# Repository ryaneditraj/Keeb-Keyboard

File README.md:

# Keeb Keyboard

A 64-key open-source mechanical keyboard: an ANSI 60% layout, a 4-key arrow cluster, a Raspberry Pi Pico, and a glue-in case. The schematic, PCB, Gerbers, and STEP file are the whole project.

Built for [Hack Club KEEB](https://keeb.hackclub.com/), a you-ship-we-ship mechanical keyboard project. This was Ryan Editraj's first PCB: a 60% he extended with arrow keys, routed in KiCad, with the Pico soldered on the front and the case modeled in Onshape.

## Demo

This repository has no firmware and no app, so there is no device screen to capture. KiCad 10 is not installed in a stock Ubuntu image, and these pictures were **plotted from the design files** by [`scripts/render_previews.py`](scripts/render_previews.py). They are not photographs and not exports from KiCad's 3D viewer.

In KiCad's default Y-up view the number row sits toward the bottom of the canvas. The plots above put that row at the top, which is how the board sits on a desk. USB leaves the far edge.

## Features

* **64 MX-style keys.** 60 keys in an ANSI 60% unit layout, plus four 1u arrow keys stepped in on the right.
* **Cherry MX PCB-mount footprints** from KiCad's keyboard library, in 1u, 1.25u, 1.5u, 1.75u, 2u, 2.25u, 2.75u, and 6.25u.
* **One diode per switch.** 64 DO-35 through-hole diodes (the KEEB parts list uses 1N4148). Cathodes face the rows, which is COL2ROW.
* **Five PCB-mount stabilizers** from marbastlib: 2u under the 2u, 2.25u, and 2.75u keys, and 6.25u under the spacebar.
* **Raspberry Pi Pico** on the common module footprint (Pico, Pico W, or Pico 2 pinout). It sits on the front of the board, in the top-right bay, with USB-C hanging off the top edge.
* **5 × 17 keyboard matrix** (ROW0–ROW4, COL0–COL16) on GP0–GP21. 64 of the 85 positions are filled.
* **Two-layer, 1.6 mm board.** 575 traces, almost all through-hole, so the design only needs two vias.
* **Fabrication outputs included.** Gerbers and Excellon drills in `PCB FILES/Output.zip`, exported from KiCad 10.0.4.
* **Onshape case.** A single open tray, about 334 × 105 × 11 mm, meant to be glued with PE foam in the bottom. No plate and no mounting holes.

## Layout

Unit sizes below are read from the footprints. The schematic does not store key legends, so this README does not invent a QWERTY print. The sizes themselves match an ANSI 60%.

| Row | Keys | Widths, left to right |
| --- | --- | --- |
| 0 | 14 | 13 × 1u, 2u |
| 1 | 14 | 1.5u, 12 × 1u, 1.5u |
| 2 | 13 | 1.75u, 11 × 1u, 2.25u |
| 3 | 12 | 2.25u, 10 × 1u, 2.75u |
| 4 | 7 | 1.25u × 3, 6.25u, 1.25u × 3 |
| Arrows | 4 | 1u up, then 1u left / down / right, set slightly below the right side |

The Pico occupies the empty bay to the right of rows 0–2, above the arrow cluster.

## Tech stack

| Piece | Choice |
| --- | --- |
| Schematic and PCB | [KiCad](https://www.kicad.org/) 10.0.4 |
| Switch footprints | `Switch_Keyboard_Cherry_MX:SW_Cherry_MX_PCB_*` |
| Stabilizers | [marbastlib](https://github.com/ebastler/marbastlib) `STAB_MX_2u` and `STAB_MX_6.25u` |
| Diodes | `Device:D_Small` on `Diode_THT:D_DO-35_SOD27_P7.62mm_Horizontal` |
| Microcontroller | Raspberry Pi Pico, `Module:RaspberryPi_Pico_Common_Unspecified` |
| Case | Onshape, exported as STEP AP242 |
| Firmware | Not in this repo yet. [KEEB's firmware guide](https://keeb.hackclub.com/docs/firmware/) points at RMK. Any scanner that can drive a COL2ROW matrix can use the pinout below. |
| CI | GitHub Actions runs `scripts/check_design.py` (Python stdlib only) |

## Quick start

1. Install [KiCad 10](https://www.kicad.org/) or newer. Older KiCad releases will not open the files.
2. Install marbastlib. In KiCad's Plugin and Content Manager, add `https://raw.githubusercontent.com/ebastler/ebastler-KiCad-repository/main/repository.json`, then install **marbastlib**. The KEEB doc [Designing the PCB](https://keeb.hackclub.com/docs/pcb-design/) has the click path.
3. Open the two design files directly. There is no `.kicad_pro` in the repo.

```text
PCB FILES/keyboard.kicad_sch
PCB FILES/keyboard.kicad_pcb
```

4. Check that the files still match the reviewed design:

```bash
python3 scripts/check_design.py
```

5. To redraw the pictures in `docs/images/`:

```bash
pip install pillow
python3 scripts/render_previews.py
```

No environment variables are required. See [.env.example](.env.example).

## Usage

### Read the board

Switches are `SW1`–`SW64`, diodes `D1`–`D64`, stabilizers `ST14`, `ST41`, `ST42`, `ST53`, and `ST58`, and the Pico is `A1`. Rows and columns are global labels (`ROW0`–`ROW4`, `COL0`–`COL16`).

### Order the PCB

`PCB FILES/Output.zip` is a KiCad 10.0.4 fabrication set:

| File | Layer |
| --- | --- |
| `keyboard-F_Cu.gbr` / `keyboard-B_Cu.gbr` | Front and back copper |
| `keyboard-F_Mask.gbr` / `keyboard-B_Mask.gbr` | Solder mask |
| `keyboard-F_Silkscreen.gbr` / `keyboard-B_Silkscreen.gbr` | Silkscreen |
| `keyboard-F_Paste.gbr` / `keyboard-B_Paste.gbr` | Paste (empty of parts; this is a through-hole board) |
| `keyboard-Edge_Cuts.gbr` | Board outline, 328.5 × 100.5 mm |
| `keyboard-PTH.drl` / `keyboard-NPTH.drl` | Plated and non-plated drills |

Ask the fab for a 2-layer, 1.6 mm board. Traces are 0.2 mm and the two vias are a 0.3 mm drill in a 0.6 mm pad, so check the fab's minimums before you order. Details are in [SECURITY.md](SECURITY.md#design-notes-that-are-not-code-vulnerabilities).

### Bill of materials

| Qty | Refs | Part | Footprint |
| --- | --- | --- | --- |
| 64 | SW1–SW64 | MX-compatible PCB-mount switch | Cherry MX PCB, see the layout table for sizes |
| 64 | D1–D64 | Small-signal diode, DO-35 (KEEB uses 1N4148) | Horizontal, 7.62 mm pitch |
| 4 | ST14, ST41, ST42, ST53 | PCB-mount MX stabilizer, 2u | marbastlib `STAB_MX_2u` |
| 1 | ST58 | PCB-mount MX stabilizer, 6.25u | marbastlib `STAB_MX_6.25u` |
| 1 | A1 | Raspberry Pi Pico (Pico W and Pico 2 fit the same footprint) | Common Pico module |
| 1 | — | Keycaps to match the unit sizes | — |
| 1 | — | Case tray, or print/cut your own from the STEP | Onshape part |

The schematic symbol for the diode is `D_Small`, not a locked manufacturer part number. Match the DO-35 footprint.

### Matrix pinout

Diode footprint pin 1 is the cathode and lands on the row. The switch connects the column to the diode anode. Drive columns, read rows (COL2ROW).

GPIO names are the official Raspberry Pi Pico pinout for these pad numbers. The unused pads in the KiCad footprint use that same numbering (`GPIO22-Pad29`, `GPIO26_ADC0-Pad31`, and so on).

| Net | Pico pin | GPIO |
| --- | --- | --- |
| ROW0 | 1 | GP0 |
| ROW1 | 2 | GP1 |
| ROW2 | 4 | GP2 |
| ROW3 | 5 | GP3 |
| ROW4 | 6 | GP4 |
| COL0 | 7 | GP5 |
| COL1 | 9 | GP6 |
| COL2 | 10 | GP7 |
| COL3 | 11 | GP8 |
| COL4 | 12 | GP9 |
| COL5 | 14 | GP10 |
| COL6 | 15 | GP11 |
| COL7 | 16 | GP12 |
| COL8 | 17 | GP13 |
| COL9 | 19 | GP14 |
| COL10 | 20 | GP15 |
| COL11 | 21 | GP16 |
| COL12 | 22 | GP17 |
| COL13 | 24 | GP18 |
| COL14 | 25 | GP19 |
| COL15 | 26 | GP20 |
| COL16 | 27 | GP21 |

Pico pins 3, 8, 13, 18, 23, 28, and 38 are ground and are tied together on the module footprint. GP22, the ADC pins, RUN, 3V3, and VBUS stay on the module. That is what you want when the Pico's own regulator and USB connector do the power.

### Open the case

Import `Case Files/keeb - Part 579.step` into Onshape, Fusion 360, or FreeCAD. The solid is one open tray: 334.4 × 104.9 × 11.0 mm outside, with a cavity 331.4 × 102.5 mm, a 4 mm floor, and walls that rise 7 mm. Wall thickness is uneven, about 1.3–1.7 mm along the length and 1.1–1.3 mm along the depth. The PCB (328.5 × 100.5 mm) drops into that cavity. The original plan is glue plus PE foam, which matches a board with no mounting holes.

## Project structure

```text
.
├── PCB FILES/
│   ├── keyboard.kicad_sch    # schematic, KiCad 10
│   ├── keyboard.kicad_pcb     # 2-layer board
│   └── Output.zip             # Gerbers and drills
├── Case Files/
│   └── keeb - Part 579.step   # Onshape tray
├── docs/images/               # plots generated from those files
├── scripts/
│   ├── check_design.py        # CI check, stdlib only
│   └── render_previews.py     # rebuild the plots (needs Pillow)
├── .github/                   # CI, issue forms, pull request template
├── LICENSE                    # MIT
├── CONTRIBUTING.md
├── CODE_OF_CONDUCT.md
├── SECURITY.md
└── .env.example               # no secrets; nothing reads this
```

Folder names keep the spaces they were published with.

## Roadmap

* Firmware and a keymap (RMK, KMK, or QMK) that uses the pinout above.
* A photo of the soldered board, once it exists. The plots in this README are not a stand-in for that.
* Mounting holes, if the case moves off glue and foam.
* A plate, if the tray gets a top half.
* A design-rule pass before the next fab order: 0.2 mm traces, 0.3 / 0.6 mm vias, and the tight outline.
* Hotswap sockets. The footprints today are soldered PCB-mount MX.

## FAQ

### What is Keeb Keyboard?

Keeb Keyboard is an open-source 64-key mechanical keyboard design by Ryan Editraj. It is a KiCad PCB for a Raspberry Pi Pico, plus an Onshape case, published for Hack Club KEEB.

### Is this a 60% keyboard?

The alpha block is a 60-key ANSI 60% (right shift is 2.75u, so there is no extra 1u key beside it). Four arrow keys bring the switch count to 64. It is not a 65% or a 75%.

### Which microcontroller does it use?

A Raspberry Pi Pico, soldered on the front of the board in the top-right bay. The footprint also fits a Pico W or a Pico 2. The matrix uses GP0 through GP21. Wireless pins are unused.

### What switches and diodes does the PCB use?

MX-compatible PCB-mount switches in Cherry MX footprints, one DO-35 small-signal diode per switch, and PCB-mount MX stabilizers on the wide keys. The KEEB build guide uses 1N4148 diodes for this footprint.

### How do I open the design files?

Install KiCad 10 or newer and marbastlib, then open `PCB FILES/keyboard.kicad_sch` and `PCB FILES/keyboard.kicad_pcb`. There is no KiCad project file to double-click.

### How do I flash the firmware?

You can't yet. Firmware is not in the repository. The [matrix pinout](#matrix-pinout) is the map a firmware needs. Hack Club's guide recommends [RMK](https://keeb.hackclub.com/docs/firmware/).

### Can I manufacture this board?

Yes. The Gerbers and drills are in `PCB FILES/Output.zip`. It is a 2-layer, 1.6 mm, through-hole keyboard PCB, 328.5 × 100.5 mm. Read the fabrication notes before ordering: thin traces, small vias, no mounting holes.

### What is the case file?

`Case Files/keeb - Part 579.step` is a single Onshape tray, roughly 334 × 105 × 11 mm, sized to hold the PCB with glue and PE foam. It is not a full sandwich case and it has no switch plate.

### Are there API keys or secrets in the repository?

No. The design files, Gerbers, STEP file, and git history were scanned. Nothing needs to be rotated. Manufacturing files are public on purpose.

### Who is allowed to build or modify this?

Anyone. The design is MIT licensed. Keep the copyright notice if you redistribute it.

### Who made this?

Ryan Editraj, while learning schematic capture, PCB layout, and CAD for Hack Club KEEB. The Pico is on the front of the board because mounting it on the back was not obvious yet, and the journaling habit started late in the build.

## Contributing

See [CONTRIBUTING.md](CONTRIBUTING.md). Small, specific pull requests are the useful ones: a footprint fix, a regenerated Gerber zip, firmware that matches this matrix, or a clearer note. Please follow the [Code of Conduct](CODE_OF_CONDUCT.md).

## License

[MIT](LICENSE) © 2026 Ryan Editraj.

## Author

**Ryan Editraj** — AI builder and tech creator.

* GitHub: [github.com/ryaneditraj](https://github.com/ryaneditraj)
* Instagram: [instagram.com/ryaneditraj](https://instagram.com/ryaneditraj)

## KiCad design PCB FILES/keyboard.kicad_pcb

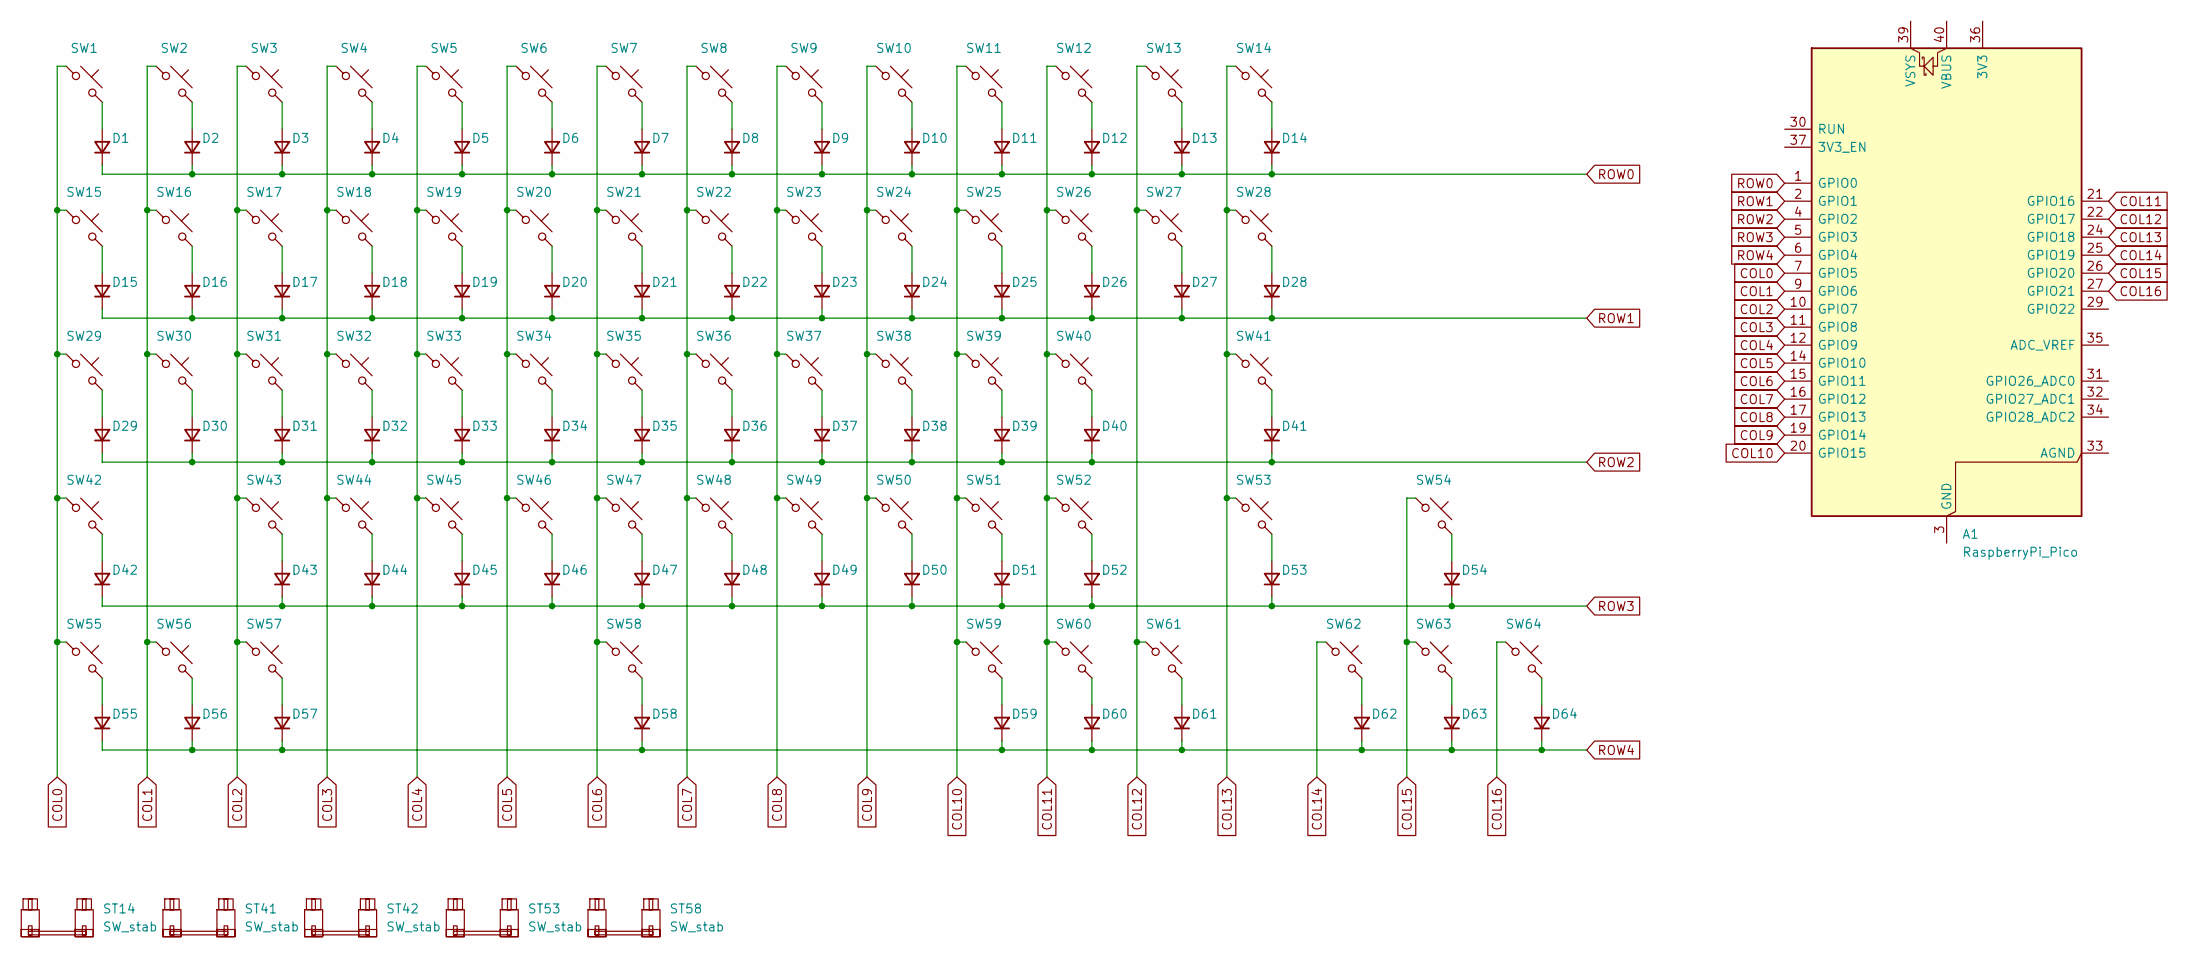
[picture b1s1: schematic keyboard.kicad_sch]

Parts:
A1: RaspberryPi_Pico; RaspberryPi_Pico_Common_Unspecified
D1, D2, D3, D4, D5, D6, D7, D8, D9, D10, D11, D12, D13, D14, D15, D16, D17, D18, D19, D20, D21, D22, D23, D24, D25, D26, D27, D28, D29, D30, D31, D32, D33, D34, D35, D36, D37, D38, D39, D40, D41, D42, D43, D44, D45, D46, D47, D48, D49, D50, D51, D52, D53, D54, D55, D56, D57, D58, D59, D60, D61, D62, D63, D64: D; D_DO-35_SOD27_P7.62mm_Horizontal
ST14, ST41, ST42, ST53: SW_stab; STAB_MX_2u
ST58: SW_stab; STAB_MX_6.25u
SW1, SW2, SW3, SW4, SW5, SW6, SW7, SW8, SW9, SW10, SW11, SW12, SW13, SW16, SW17, SW18, SW19, SW20, SW21, SW22, SW23, SW24, SW25, SW26, SW27, SW30, SW31, SW32, SW33, SW34, SW35, SW36, SW37, SW38, SW39, SW40, SW43, SW44, SW45, SW46, SW47, SW48, SW49, SW50, SW51, SW52, SW54, SW62, SW63, SW64: SW_Push; SW_Cherry_MX_PCB_1.00u
SW14: SW_Push; SW_Cherry_MX_PCB_2.00u
SW15, SW28: SW_Push; SW_Cherry_MX_PCB_1.50u
SW29: SW_Push; SW_Cherry_MX_PCB_1.75u
SW41, SW42: SW_Push; SW_Cherry_MX_PCB_2.25u
SW53: SW_Push; SW_Cherry_MX_PCB_2.75u
SW55, SW56, SW57, SW59, SW60, SW61: SW_Push; SW_Cherry_MX_PCB_1.25u
SW58: SW_Push; SW_Cherry_MX_PCB_6.25u

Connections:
COL0: A1.7 (GPIO5), SW1.1, SW15.1, SW29.1, SW42.1, SW55.1
COL1: A1.9 (GPIO6), SW2.1, SW16.1, SW30.1, SW56.1
COL2: A1.10 (GPIO7), SW3.1, SW17.1, SW31.1, SW43.1, SW57.1
COL3: A1.11 (GPIO8), SW4.1, SW18.1, SW32.1, SW44.1
COL4: A1.12 (GPIO9), SW5.1, SW19.1, SW33.1, SW45.1
COL5: A1.14 (GPIO10), SW6.1, SW20.1, SW34.1, SW46.1
COL6: A1.15 (GPIO11), SW7.1, SW21.1, SW35.1, SW47.1, SW58.1
COL7: A1.16 (GPIO12), SW8.1, SW22.1, SW36.1, SW48.1
COL8: A1.17 (GPIO13), SW9.1, SW23.1, SW37.1, SW49.1
COL9: A1.19 (GPIO14), SW10.1, SW24.1, SW38.1, SW50.1
COL10: A1.20 (GPIO15), SW11.1, SW25.1, SW39.1, SW51.1, SW59.1
COL11: A1.21 (GPIO16), SW12.1, SW26.1, SW40.1, SW52.1, SW60.1
COL12: A1.22 (GPIO17), SW13.1, SW27.1, SW61.1
COL13: A1.24 (GPIO18), SW14.1, SW28.1, SW41.1, SW53.1
COL14: A1.25 (GPIO19), SW62.1
COL15: A1.26 (GPIO20), SW54.1, SW63.1
COL16: A1.27 (GPIO21), SW64.1
unnamed: A1.3 (GND), A1.8 (GND), A1.13 (GND), A1.18 (GND), A1.23 (GND), A1.28 (GND), A1.38 (GND)
unnamed: D1.2 (A), SW1.2
unnamed: D2.2 (A), SW2.2
unnamed: D3.2 (A), SW3.2
unnamed: D4.2 (A), SW4.2
unnamed: D5.2 (A), SW5.2
unnamed: D6.2 (A), SW6.2
unnamed: D7.2 (A), SW7.2
unnamed: D8.2 (A), SW8.2
unnamed: D9.2 (A), SW9.2
unnamed: D10.2 (A), SW10.2
unnamed: D11.2 (A), SW11.2
unnamed: D12.2 (A), SW12.2
unnamed: D13.2 (A), SW13.2
unnamed: D14.2 (A), SW14.2
unnamed: D15.2 (A), SW15.2
unnamed: D16.2 (A), SW16.2
unnamed: D17.2 (A), SW17.2
unnamed: D18.2 (A), SW18.2
unnamed: D19.2 (A), SW19.2
unnamed: D20.2 (A), SW20.2
unnamed: D21.2 (A), SW21.2
unnamed: D22.2 (A), SW22.2
unnamed: D23.2 (A), SW23.2
unnamed: D24.2 (A), SW24.2
unnamed: D25.2 (A), SW25.2
unnamed: D26.2 (A), SW26.2
unnamed: D27.2 (A), SW27.2
unnamed: D28.2 (A), SW28.2
unnamed: D29.2 (A), SW29.2
unnamed: D30.2 (A), SW30.2
unnamed: D31.2 (A), SW31.2
unnamed: D32.2 (A), SW32.2
unnamed: D33.2 (A), SW33.2
unnamed: D34.2 (A), SW34.2
unnamed: D35.2 (A), SW35.2
unnamed: D36.2 (A), SW36.2
unnamed: D37.2 (A), SW37.2
unnamed: D38.2 (A), SW38.2
unnamed: D39.2 (A), SW39.2
unnamed: D40.2 (A), SW40.2
unnamed: D41.2 (A), SW41.2
unnamed: D42.2 (A), SW42.2
unnamed: D43.2 (A), SW43.2
unnamed: D44.2 (A), SW44.2
unnamed: D45.2 (A), SW45.2
unnamed: D46.2 (A), SW46.2
unnamed: D47.2 (A), SW47.2
unnamed: D48.2 (A), SW48.2
unnamed: D49.2 (A), SW49.2
unnamed: D50.2 (A), SW50.2
unnamed: D51.2 (A), SW51.2
unnamed: D52.2 (A), SW52.2
unnamed: D53.2 (A), SW53.2
unnamed: D54.2 (A), SW54.2
unnamed: D55.2 (A), SW55.2
unnamed: D56.2 (A), SW56.2
unnamed: D57.2 (A), SW57.2
unnamed: D58.2 (A), SW58.2
unnamed: D59.2 (A), SW59.2
unnamed: D60.2 (A), SW60.2
unnamed: D61.2 (A), SW61.2
unnamed: D62.2 (A), SW62.2
unnamed: D63.2 (A), SW63.2
unnamed: D64.2 (A), SW64.2
ROW0: A1.1 (GPIO0), D1.1 (K), D2.1 (K), D3.1 (K), D4.1 (K), D5.1 (K), D6.1 (K), D7.1 (K), D8.1 (K), D9.1 (K), D10.1 (K), D11.1 (K), D12.1 (K), D13.1 (K), D14.1 (K)
ROW1: A1.2 (GPIO1), D15.1 (K), D16.1 (K), D17.1 (K), D18.1 (K), D19.1 (K), D20.1 (K), D21.1 (K), D22.1 (K), D23.1 (K), D24.1 (K), D25.1 (K), D26.1 (K), D27.1 (K), D28.1 (K)
ROW2: A1.4 (GPIO2), D29.1 (K), D30.1 (K), D31.1 (K), D32.1 (K), D33.1 (K), D34.1 (K), D35.1 (K), D36.1 (K), D37.1 (K), D38.1 (K), D39.1 (K), D40.1 (K), D41.1 (K)
ROW3: A1.5 (GPIO3), D42.1 (K), D43.1 (K), D44.1 (K), D45.1 (K), D46.1 (K), D47.1 (K), D48.1 (K), D49.1 (K), D50.1 (K), D51.1 (K), D52.1 (K), D53.1 (K), D54.1 (K)
ROW4: A1.6 (GPIO4), D55.1 (K), D56.1 (K), D57.1 (K), D58.1 (K), D59.1 (K), D60.1 (K), D61.1 (K), D62.1 (K), D63.1 (K), D64.1 (K)

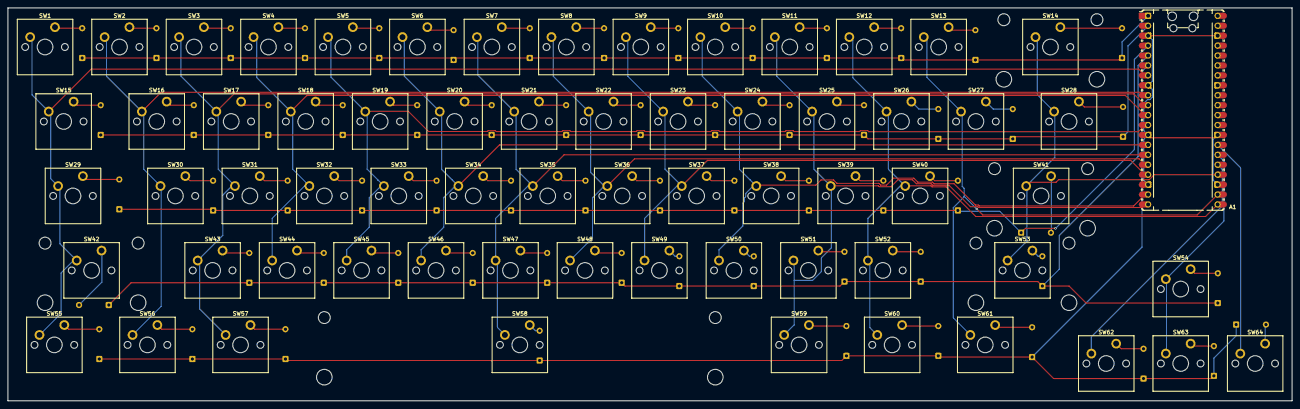
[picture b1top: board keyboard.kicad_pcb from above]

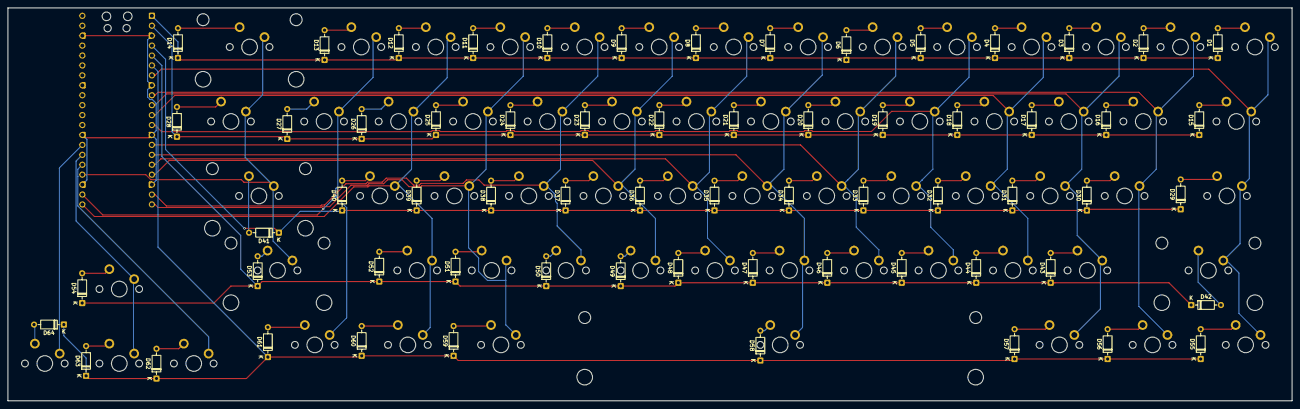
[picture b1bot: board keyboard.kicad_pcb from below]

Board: 2 copper layers, 328.5 x 100.5 mm, 134 parts (64 on the bottom side), 87 nets.

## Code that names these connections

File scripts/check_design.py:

#!/usr/bin/env python3
"""Sanity-check the keyboard design files.

Stdlib only. Confirms the KiCad board still parses as the reviewed
64-key design, the fabrication zip has the expected Gerbers and no
macOS junk, and text files do not contain credential-shaped strings.
"""

from __future__ import annotations

import re
import sys
import zipfile
from pathlib import Path

ROOT = Path(__file__).resolve().parents[1]
PCB_PATH = ROOT / "PCB FILES" / "keyboard.kicad_pcb"
SCH_PATH = ROOT / "PCB FILES" / "keyboard.kicad_sch"
ZIP_PATH = ROOT / "PCB FILES" / "Output.zip"
STEP_PATH = ROOT / "Case Files" / "keeb - Part 579.step"

GERBERS = {
    "Output/keyboard-F_Cu.gbr",
    "Output/keyboard-B_Cu.gbr",
    "Output/keyboard-F_Mask.gbr",
    "Output/keyboard-B_Mask.gbr",
    "Output/keyboard-F_Silkscreen.gbr",
    "Output/keyboard-B_Silkscreen.gbr",
    "Output/keyboard-F_Paste.gbr",
    "Output/keyboard-B_Paste.gbr",
    "Output/keyboard-Edge_Cuts.gbr",
    "Output/keyboard-PTH.drl",
    "Output/keyboard-NPTH.drl",
}

SECRET_PATTERNS = (
    re.compile(r"AKIA[0-9A-Z]{16}"),
    re.compile(r"ghp_[A-Za-z0-9]{20,}"),
    re.compile(r"github_pat_[A-Za-z0-9_]{20,}"),
    re.compile(r"sk-[A-Za-z0-9]{20,}"),
    re.compile(r"xox[baprs]-[A-Za-z0-9-]{10,}"),
    re.compile(r"-----BEGIN (?:RSA |OPENSSH |EC )?PRIVATE KEY-----"),
    re.compile(r"(?i)\b(api[_-]?key|secret|password|token)\b\s*[:=]\s*['\"][^'\"]+['\"]"),
)

TEXT_SUFFIXES = {".md", ".py", ".yml", ".yaml", ".txt", ".kicad_pcb", ".kicad_sch", ".example", ".gitignore"}


def parse_sexpr(text: str) -> list:
    tokens = re.findall(r'\(|\)|"(?:\\.|[^"\\])*"|[^\s()]+', text)

    def rec(i: int):
        node: list = []
        while i < len(tokens):
            token = tokens[i]
            if token == "(":
                child, i = rec(i + 1)
                node.append(child)
            elif token == ")":
                return node, i + 1
            else:
                if len(token) >= 2 and token[0] == '"' and token[-1] == '"':
                    token = token[1:-1]
                node.append(token)
                i += 1
        return node, i

    tree, _ = rec(1)
    return tree


def prop(node: list, key: str):
    for item in node:
        if isinstance(item, list) and len(item) > 2 and item[0] == "property" and item[1] == key:
            return item[2]
    return None


def child(node: list, name: str):
    for item in node:
        if isinstance(item, list) and item and item[0] == name:
            return item
    return None


class Report:
    def __init__(self):
        self.errors: list[str] = []

    def check(self, condition: bool, message: str):
        if not condition:
            self.errors.append(message)

    def fail(self, message: str):
        self.errors.append(message)


def pad_nets(footprint: list) -> dict[str, str]:
    nets: dict[str, str] = {}
    for pad in footprint:
        if not isinstance(pad, list) or not pad or pad[0] != "pad":
            continue
        net = child(pad, "net")
        if net and len(net) > 1:
            nets.setdefault(str(pad[1]), net[1])
    return nets


def check_board(report: Report):
    report.check(PCB_PATH.is_file(), f"missing {PCB_PATH.name}")
    report.check(SCH_PATH.is_file(), f"missing {SCH_PATH.name}")
    if not PCB_PATH.is_file() or not SCH_PATH.is_file():
        return
    pcb = parse_sexpr(PCB_PATH.read_text(encoding="utf-8"))
    sch = parse_sexpr(SCH_PATH.read_text(encoding="utf-8"))
    report.check(pcb and pcb[0] == "kicad_pcb", "PCB root is not kicad_pcb")
    report.check(sch and sch[0] == "kicad_sch", "schematic root is not kicad_sch")

    footprints = [node for node in pcb if isinstance(node, list) and node and node[0] == "footprint"]
    counts = {"SW": 0, "D": 0, "ST": 0, "A": 0}
    pico_nets: dict[str, str] = {}
    diode_rows = 0
    switch_cols = 0
    for footprint in footprints:
        ref = prop(footprint, "Reference") or ""
        prefix = re.match(r"[A-Z]+", ref)
        if prefix:
            counts[prefix.group(0)] = counts.get(prefix.group(0), 0) + 1
        nets = pad_nets(footprint)
        if ref == "A1":
            pico_nets = nets
        if ref.startswith("D") and nets.get("1", "").startswith("ROW") and nets.get("2", "").startswith("Net-(D"):
            diode_rows += 1
        if ref.startswith("SW") and any(net.startswith("COL") for net in nets.values()):
            switch_cols += 1

    report.check(counts.get("SW") == 64, f"expected 64 switches, found {counts.get('SW')}")
    report.check(counts.get("D") == 64, f"expected 64 diodes, found {counts.get('D')}")
    report.check(counts.get("ST") == 5, f"expected 5 stabilizers, found {counts.get('ST')}")
    report.check(counts.get("A") == 1, f"expected 1 Pico, found {counts.get('A')}")
    report.check(diode_rows == 64, f"expected 64 diodes with cathode on a ROW, found {diode_rows}")
    report.check(switch_cols == 64, f"expected 64 switches on a COL net, found {switch_cols}")

    row_pins = {1: "ROW0", 2: "ROW1", 4: "ROW2", 5: "ROW3", 6: "ROW4"}
    for pin, net in row_pins.items():
        report.check(pico_nets.get(str(pin)) == net, f"Pico pin {pin} should be {net}")
    # Pico pins 7, 9-12, 14-17, 19-22, 24-27 are COL0-COL16 in order, skipping GND pins.
    column_pins = [7, 9, 10, 11, 12, 14, 15, 16, 17, 19, 20, 21, 22, 24, 25, 26, 27]
    for index, pin in enumerate(column_pins):
        report.check(pico_nets.get(str(pin)) == f"COL{index}", f"Pico pin {pin} should be COL{index}")

    outline = None
    for node in pcb:
        if isinstance(node, list) and node and node[0] == "gr_rect":
            layer = child(node, "layer")
            if layer and layer[1] == "Edge.Cuts":
                start = child(node, "start")
                end = child(node, "end")
                outline = tuple(float(value) for value in (start[1], start[2], end[1], end[2]))
    report.check(outline == (-9.5, -10.0, 319.0, 90.5), f"unexpected board outline {outline}")

    segments = [node for node in pcb if isinstance(node, list) and node and node[0] == "segment"]
    report.check(len(segments) == 575, f"expected 575 copper segments, found {len(segments)}")
    placed = [
        node
        for node in sch
        if isinstance(node, list) and node and node[0] == "symbol" and child(node, "lib_id")
    ]
    report.check(len(placed) == 134, f"expected 134 placed schematic symbols, found {len(placed)}")


def check_fabrication(report: Report):
    report.check(ZIP_PATH.is_file(), "missing Gerber zip")
    report.check(STEP_PATH.is_file(), "missing case STEP")
    if STEP_PATH.is_file():
        head = STEP_PATH.read_text(encoding="utf-8", errors="replace")[:20]
        report.check(head.startswith("ISO-10303-21"), "case file is not a STEP file")
    if not ZIP_PATH.is_file():
        return
    with zipfile.ZipFile(ZIP_PATH) as archive:
        names = set(archive.namelist())
        report.check("__MACOSX/" not in "".join(names), "Gerber zip still contains __MACOSX resource forks")
        for name in names:
            if name.endswith("/"):
                continue
            report.check(name in GERBERS, f"unexpected fabrication file {name}")
            info = archive.getinfo(name)
            report.check(info.file_size > 0, f"empty fabrication file {name}")
        report.check(GERBERS <= names, f"Gerber zip is missing {sorted(GERBERS - names)}")


def check_secrets(report: Report):
    for path in ROOT.rglob("*"):
        if not path.is_file():
            continue
        if ".git" in path.parts or "docs/images" in str(path):
            continue
        if path.name == ".env":
            report.fail(f"secret file present: {path.relative_to(ROOT)}")
        if path.suffix.lower() not in TEXT_SUFFIXES and path.name not in {".gitignore", ".env.example"}:
            continue
        text = path.read_text(encoding="utf-8", errors="replace")
        for pattern in SECRET_PATTERNS:
            if pattern.search(text):
                report.fail(f"credential-shaped string in {path.relative_to(ROOT)}")
                break


def main():
    report = Report()
    check_board(report)
    check_fabrication(report)
    check_secrets(report)
    if report.errors:
        for error in report.errors:
            print(f"FAIL {error}")
        return 1
    print("design check passed")
    return 0


if __name__ == "__main__":
    sys.exit(main())

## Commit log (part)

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2026-06-23 Enhance README with project details and suggestions
    Expanded project description and added suggestions for documentation improvements.
